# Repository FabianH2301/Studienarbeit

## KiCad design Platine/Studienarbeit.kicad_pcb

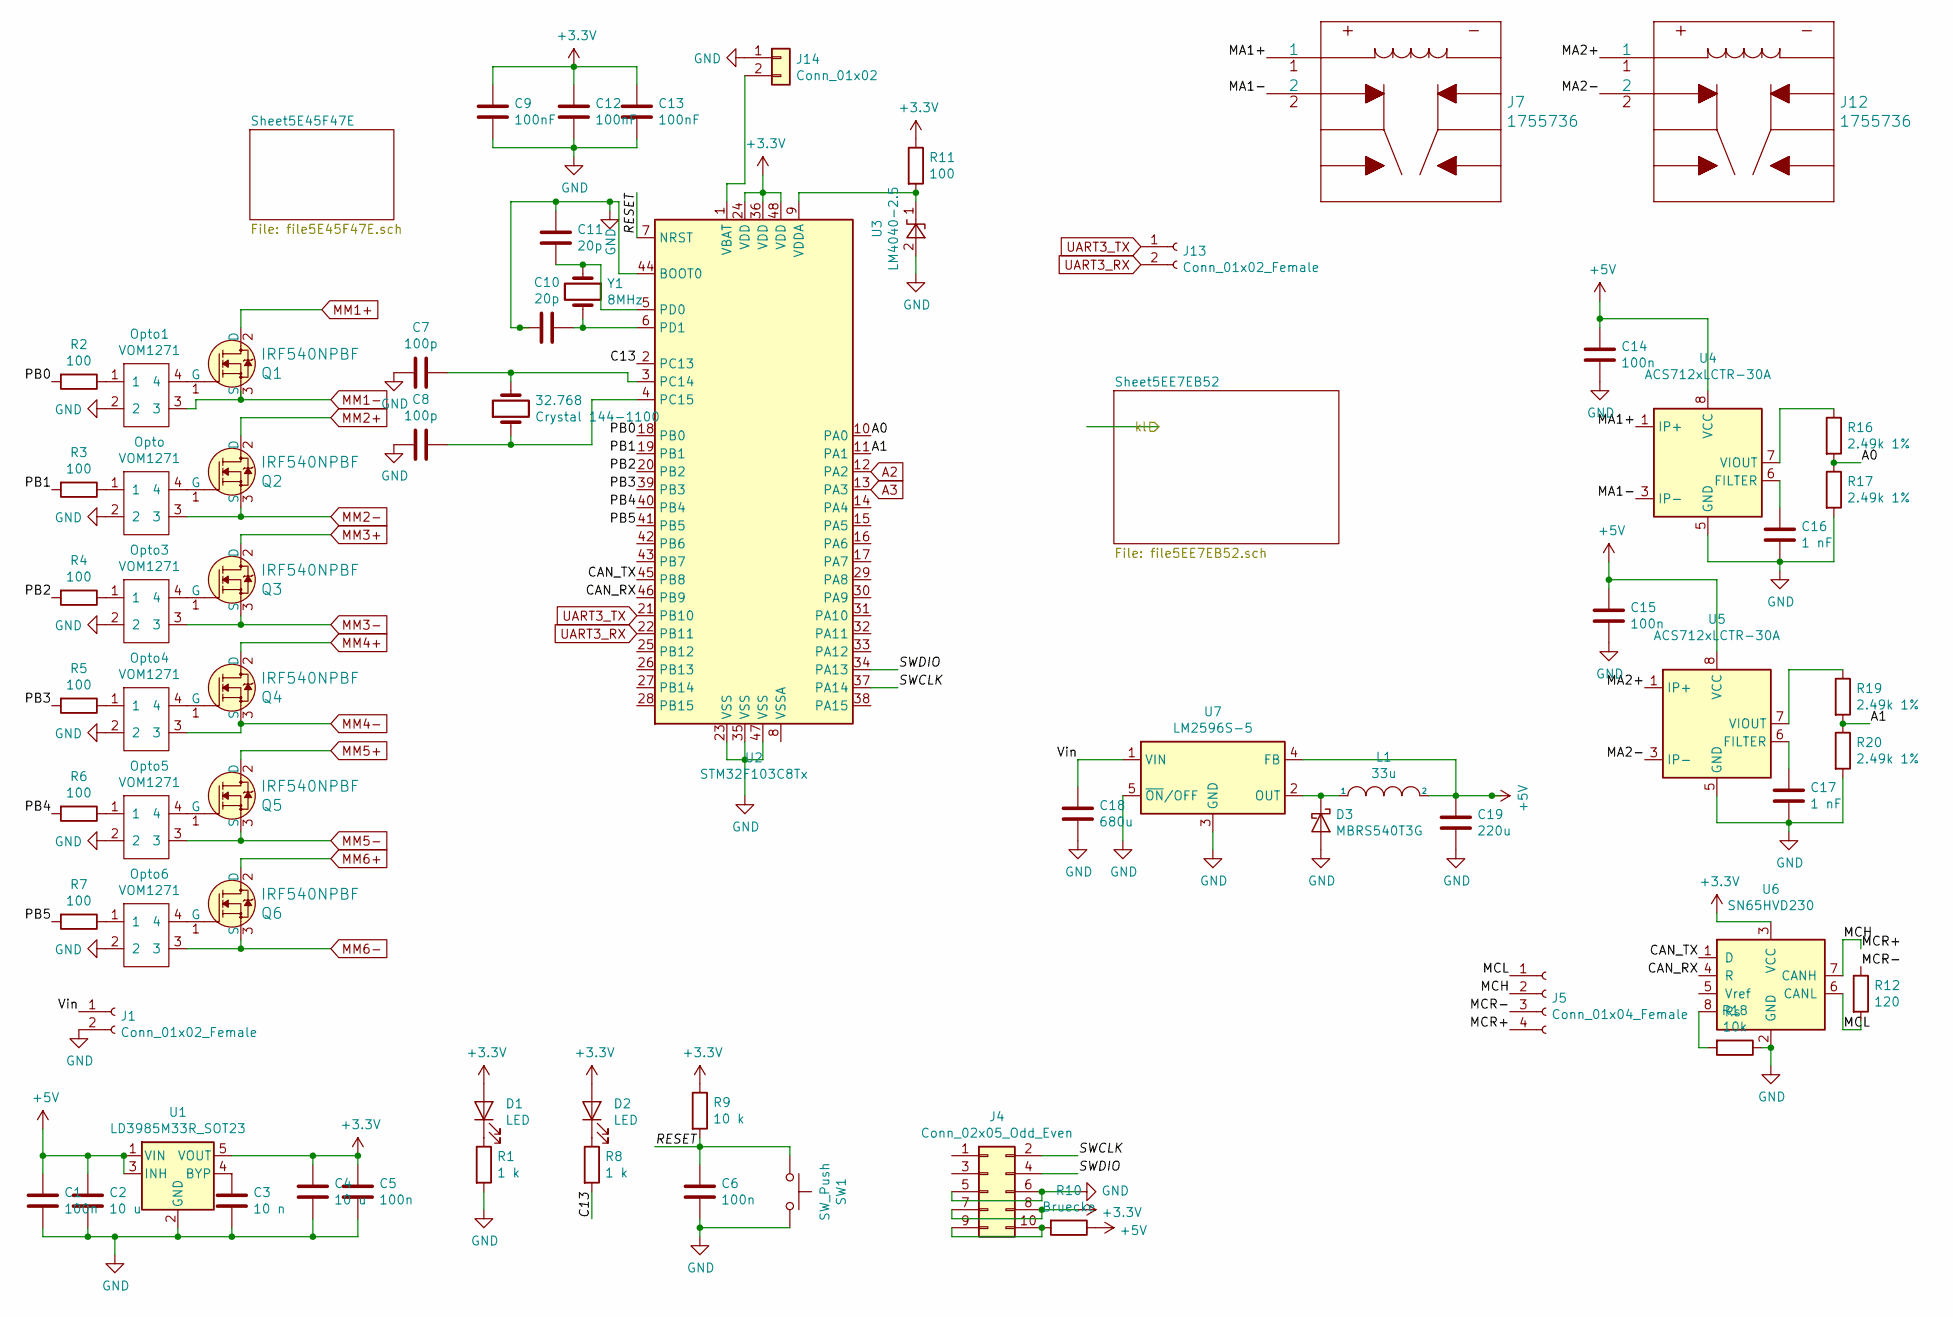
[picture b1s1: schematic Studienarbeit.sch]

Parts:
32.768: Crystal 144-1100; Crystal_SMD_2520-4Pin_2.5x2.0mm
C1, C5, C14, C15: 100n; C_0805_2012Metric; LCSC C136621
C2, C4: 10 u; C_0805_2012Metric; LCSC C15850
C3: 10 n; C_0805_2012Metric
C6: 100n; C_0805_2012Metric
C7, C8: 100p; C_0805_2012Metric
C9, C12, C13: 100nF; C_0805_2012Metric; LCSC C136621
C10, C11: 20p; C_0805_2012Metric
C16, C17: 1 nF; C_0805_2012Metric
C18: 680u; C_Elec_10x10.2
C19: 220u; C_Elec_8x6.2
D1, D2: LED; LED_0603_1608Metric; LCSC C2286
D3: MBRS540T3G; D_SMC; LCSC C31849
J1, J13: Conn_01x02_Female; JST_XH_B2B-XH-A_1x02_P2.50mm_Vertical
J4: Conn_02x05_Odd_Even; PinHeader_2x05_P2.54mm_Vertical
J5: Conn_01x04_Female; JST_XH_B4B-XH-A_1x04_P2.50mm_Vertical
J7, J12: 1755736; PhoenixContact1755736
J14: Conn_01x02; PinHeader_1x02_P2.54mm_Vertical
L1: 33u; L_Wuerth_WE-PD-Typ-LS
Opto, Opto1, Opto3, Opto4, Opto5, Opto6: VOM1271; LCSC C146286
Q1, Q2, Q3, Q4, Q5, Q6: IRF540NPBF; TO-220-3_Vertical; MPN IRF540NPBF; Digi-Key_PN IRF540NPBF-ND
R1, R8: 1 k; R_0805_2012Metric; LCSC C17513
R2: 100; R_0805_2012Metric
R3, R4, R5, R6, R7, R11: 100; R_0805_2012Metric; LCSC C17408
R9: 10 k; R_0805_2012Metric; LCSC C17414
R10: Bruecke; R_0805_2012Metric
R12: 120; R_0805_2012Metric; LCSC C17437
R16, R17, R19, R20: 2.49k 1%; R_0805_2012Metric; LCSC C17408
R18: 10k; R_0805_2012Metric; LCSC C17414
SW1: SW_Push; SW_SPST_B3S-1000
U1: LD3985M33R_SOT23; SOT-23-5; LCSC C46243
U2: STM32F103C8Tx; LQFP-48_7x7mm_P0.5mm; LCSC C8734
U3: LM4040-2.5; SOT-23
U4, U5: ACS712xLCTR-30A; SOIC-8_3.9x4.9mm_P1.27mm; LCSC C9932
U6: SN65HVD230; SOIC-8_3.9x4.9mm_P1.27mm; LCSC C12084
U7: LM2596S-5; TO-263-5_TabPin3; LCSC C10002
Y1: 8MHz; Crystal_HC49-4H_Vertical

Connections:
+3V3: C4.1, C5.1, C9.1, C12.1, C13.1, D1.2 (A), D2.2 (A), J4.7, J4.8, R9.1, R11.1, U1.5 (VOUT), U2.24 (VDD), U2.36 (VDD), U2.48 (VDD), U6.3 (VCC)
+5V: C1.1, C2.1, C14.2, C15.2, C19.1, L1.2, R10.1, U1.1 (VIN), U1.3 (INH), U4.8 (VCC), U5.8 (VCC), U7.4 (FB); also elsewhere on the board
/A0: R16.2, R17.1, U2.10 (PA0)
/A1: R19.2, R20.1, U2.11 (PA1)
/C13: R8.2, U2.2 (PC13)
/CAN_RX: U2.46 (PB9), U6.4 (R)
/CAN_TX: U2.45 (PB8), U6.1 (D)
/MA1+: J7.1, U4.1 (IP+), U4.2 (IP+)
/MA1-: J7.2, U4.3 (IP-), U4.4 (IP-)
/MA2+: J12.1, U5.1 (IP+), U5.2 (IP+)
/MA2-: J12.2, U5.3 (IP-), U5.4 (IP-)
/MCH: J5.2, J5.4, U6.7 (CANH)
/MCL: J5.1, R12.2, U6.6 (CANL)
/MCR-: J5.3, R12.1
/PB0: R2.2, U2.18 (PB0)
/PB1: R3.2, U2.19 (PB1)
/PB2: R4.2, U2.20 (PB2)
/PB3: R5.2, U2.39 (PB3)
/PB4: R6.2, U2.40 (PB4)
/PB5: R7.2, U2.41 (PB5)
/RESET: C6.1, R9.2, SW1.1, U2.7 (NRST)
/SWCLK: J4.2, U2.37 (PA14)
/SWDIO: J4.4, U2.34 (PA13)
/Vin: C18.1, J1.1, U7.1 (VIN)
A2: U2.12 (PA2); also elsewhere on the board
A3: U2.13 (PA3); also elsewhere on the board
GND: C1.2, C2.2, C3.2, C4.2, C5.2, C6.2, C7.2, C8.2, C9.2, C10.1, C11.1, C12.2, C13.2, C14.1, C15.1, C16.1, C17.1, C18.2, C19.2, D3.2 (A), J1.2, J4.5, J4.6, J14.1, Opto.2, Opto1.2, Opto3.2, Opto4.2, Opto5.2, Opto6.2, R1.2, R17.2, R18.1, R20.2, SW1.2, U1.2 (GND), U2.23 (VSS), U2.35 (VSS), U2.44 (BOOT0), U2.47 (VSS), U3.2 (A), U4.5 (GND), U5.5 (GND), U6.2 (GND), U7.3 (GND), U7.5 (~ON~/OFF); also elsewhere on the board
MM1+: Q1.2 (D); also elsewhere on the board
MM1-: Opto1.3, Q1.3 (S); also elsewhere on the board
MM2+: Q2.2 (D); also elsewhere on the board
MM2-: Opto.3, Q2.3 (S); also elsewhere on the board
MM3+: Q3.2 (D); also elsewhere on the board
MM3-: Opto3.3, Q3.3 (S); also elsewhere on the board
MM4+: Q4.2 (D); also elsewhere on the board
MM4-: Opto4.3, Q4.3 (S); also elsewhere on the board
MM5+: Q5.2 (D); also elsewhere on the board
MM5-: Opto5.3, Q5.3 (S); also elsewhere on the board
MM6+: Q6.2 (D); also elsewhere on the board
MM6-: Opto6.3, Q6.3 (S); also elsewhere on the board
unnamed: 32.768.1, C8.1, U2.4 (PC15)
unnamed: 32.768.2, C7.1, U2.3 (PC14)
unnamed: C3.1, U1.4 (BYP)
unnamed: C10.2, U2.6 (PD1), Y1.2
unnamed: C11.2, U2.5 (PD0), Y1.1
unnamed: C16.2, U4.6 (FILTER)
unnamed: C17.2, U5.6 (FILTER)
unnamed: D1.1 (K), R1.1
unnamed: D2.1 (K), R8.1
unnamed: D3.1 (K), L1.1, U7.2 (OUT)
unnamed: J4.9, J4.10, R10.2
unnamed: J14.2, U2.1 (VBAT)
unnamed: Opto1.1, R2.1
unnamed: Opto1.4, Q1.1 (G)
unnamed 72: Opto.1, R3.1; also elsewhere on the board
unnamed 73: Opto.4, Q2.1 (G); also elsewhere on the board
unnamed: Opto3.1, R4.1
unnamed: Opto3.4, Q3.1 (G)
unnamed: Opto4.1, R5.1
unnamed: Opto4.4, Q4.1 (G)
unnamed: Opto5.1, R6.1
unnamed: Opto5.4, Q5.1 (G)
unnamed: Opto6.1, R7.1
unnamed: Opto6.4, Q6.1 (G)
unnamed: R11.2, U2.9 (VDDA), U3.1 (K)
unnamed: R16.1, U4.7 (VIOUT)
unnamed: R18.2, U6.8 (Rs)
unnamed: R19.1, U5.7 (VIOUT)
UART3_RX: J13.2, U2.22 (PB11)
UART3_TX: J13.1, U2.21 (PB10)

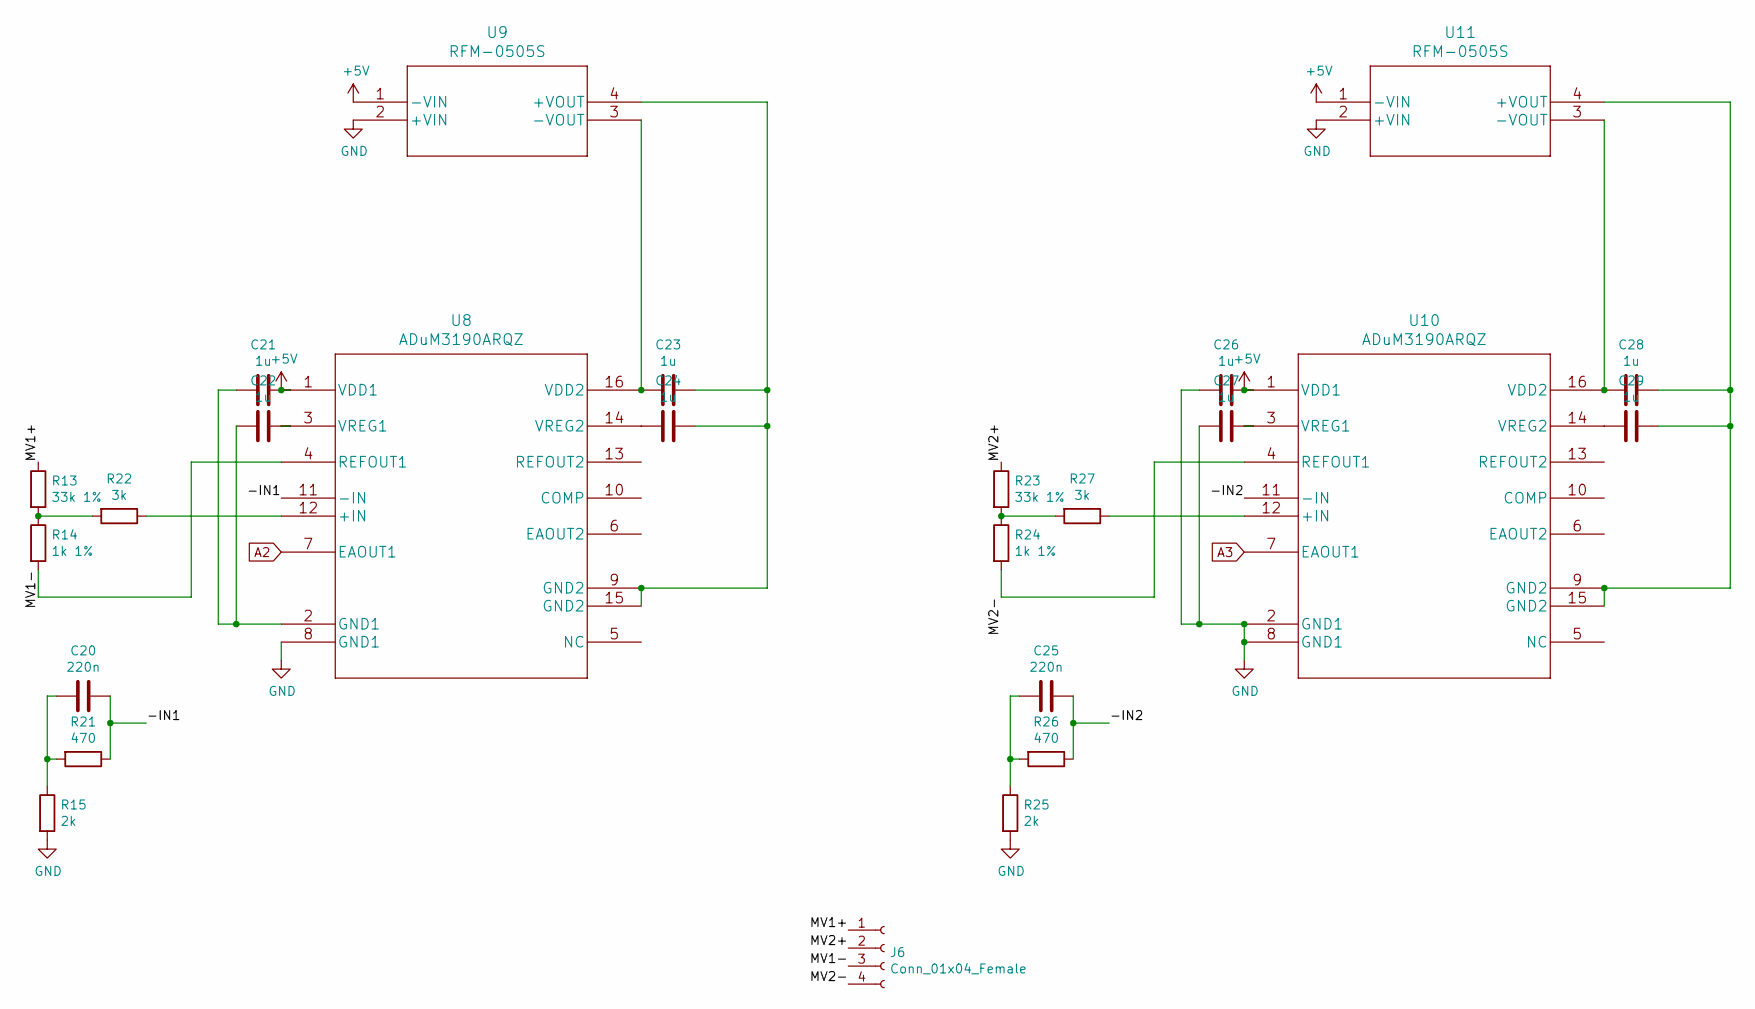
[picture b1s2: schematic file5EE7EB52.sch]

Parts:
C20, C25: 220n; C_0805_2012Metric; LCSC C5378
C21, C22, C23, C24, C26, C27, C28, C29: 1u; C_0805_2012Metric; LCSC C28323
J6: Conn_01x04_Female; JST_XH_B4B-XH-A_1x04_P2.50mm_Vertical
R13, R23: 33k 1%; R_0805_2012Metric; LCSC C17633
R14, R24: 1k 1%; R_0805_2012Metric; LCSC C17513
R15, R25: 2k; R_0805_2012Metric; LCSC C17604
R21, R26: 470; R_0805_2012Metric; LCSC C17710
R22, R27: 3k; R_0805_2012Metric; LCSC C17661
U8, U10: ADuM3190ARQZ
U9, U11: RFM-0505S

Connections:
+5V: C21.2, C26.2, U8.1 (VDD1), U9.1 (-VIN), U10.1 (VDD1), U11.1 (-VIN); also elsewhere on the board
/Sheet5EE7EB52/-IN1: C20.1, R21.1, U8.11 (-IN)
/Sheet5EE7EB52/-IN2: C25.1, R26.1, U10.11 (-IN)
/Sheet5EE7EB52/MV1+: J6.1, R13.1
/Sheet5EE7EB52/MV1-: J6.3, R14.2, U8.4 (REFOUT1)
/Sheet5EE7EB52/MV2+: J6.2, R23.1
/Sheet5EE7EB52/MV2-: J6.4, R24.2, U10.4 (REFOUT1)
A2: U8.7 (EAOUT1); also elsewhere on the board
A3: U10.7 (EAOUT1); also elsewhere on the board
GND: C26.1, C27.1, R15.2, R25.2, U8.8 (GND1), U9.2 (+VIN), U10.2 (GND1), U10.8 (GND1), U11.2 (+VIN); also elsewhere on the board
unnamed: C20.2, R15.1, R21.2
unnamed: C21.1, C22.1, U8.2 (GND1)
unnamed: C22.2, U8.3 (VREG1)
unnamed: C23.1, U8.16 (VDD2), U9.3 (-VOUT)
unnamed: C23.2, C24.2, U8.9 (GND2), U8.15 (GND2), U9.4 (+VOUT)
unnamed: C24.1, U8.14 (VREG2)
unnamed: C25.2, R25.1, R26.2
unnamed: C27.2, U10.3 (VREG1)
unnamed: C28.1, U10.16 (VDD2), U11.3 (-VOUT)
unnamed: C28.2, C29.2, U10.9 (GND2), U10.15 (GND2), U11.4 (+VOUT)
unnamed: C29.1, U10.14 (VREG2)
unnamed: R13.2, R14.1, R22.2
unnamed: R22.1, U8.12 (+IN)
unnamed: R23.2, R24.1, R27.2
unnamed: R27.1, U10.12 (+IN)

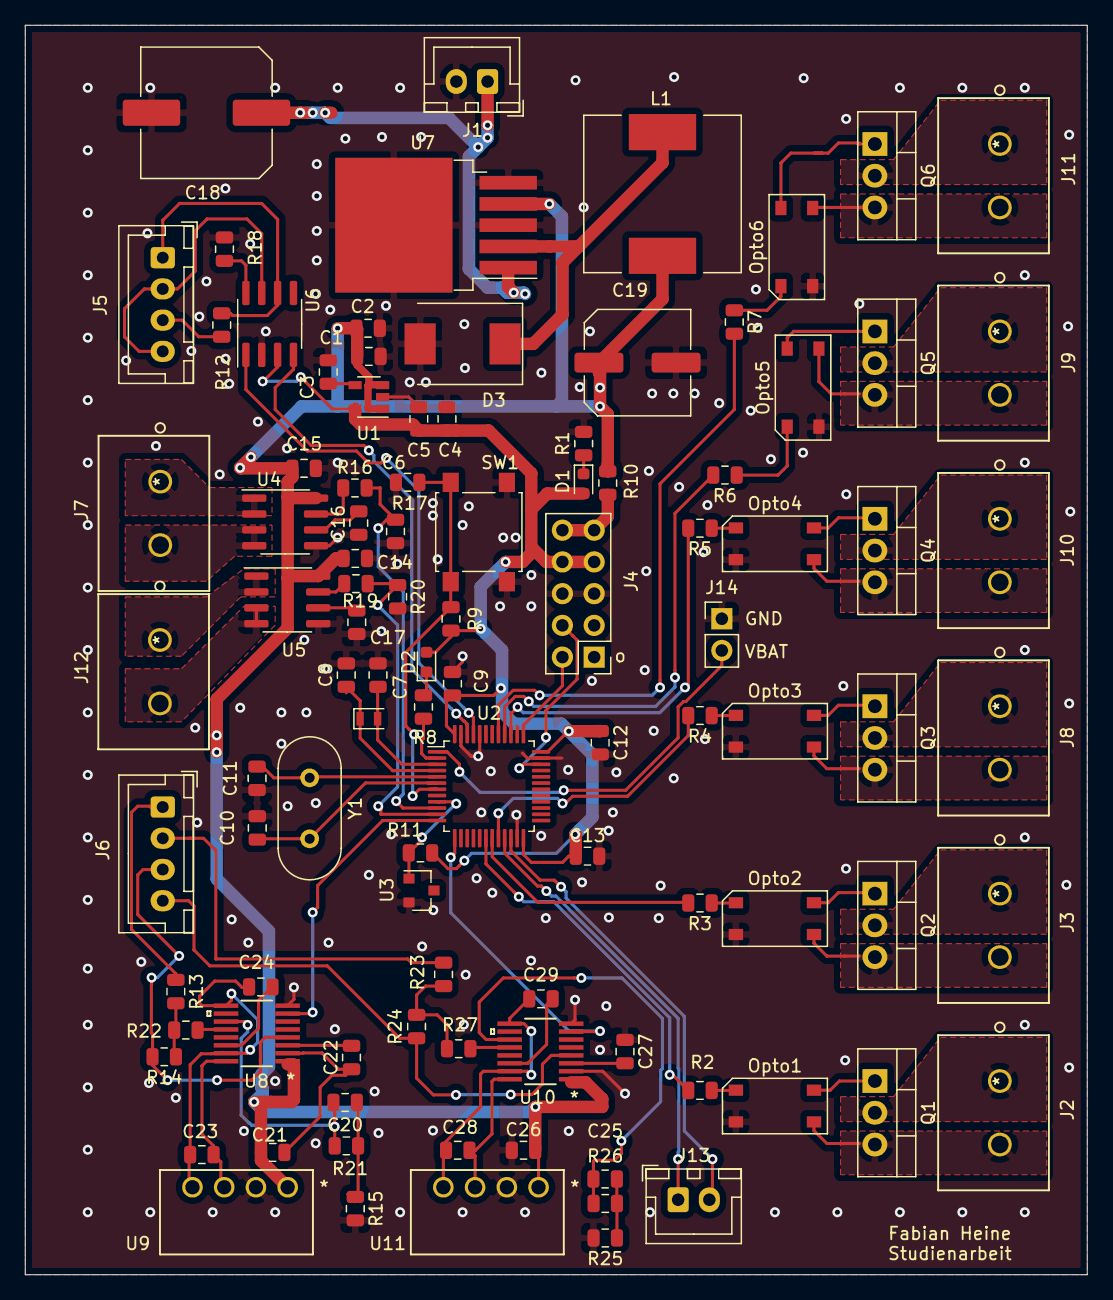
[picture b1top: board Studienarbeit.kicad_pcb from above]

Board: 2 copper layers, 85.0 x 100.0 mm, 100 parts (0 on the bottom side), 90 nets.

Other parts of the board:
J2, J3, J8, J9, J10, J11: 1755736; PhoenixContact1755736
Opto2: VOM1271

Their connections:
GND: Opto2.2; also elsewhere on the board
MM1+: J2.1; also elsewhere on the board
MM1-: J2.2; also elsewhere on the board
MM2+: J3.1; also elsewhere on the board
MM2-: J3.2, Opto2.3; also elsewhere on the board
MM3+: J8.1; also elsewhere on the board
MM3-: J8.2; also elsewhere on the board
MM4+: J10.1; also elsewhere on the board
MM4-: J10.2; also elsewhere on the board
MM5+: J9.1; also elsewhere on the board
MM5-: J9.2; also elsewhere on the board
MM6+: J11.1; also elsewhere on the board
MM6-: J11.2; also elsewhere on the board
unnamed 72: Opto2.1; also elsewhere on the board
unnamed 73: Opto2.4; also elsewhere on the board

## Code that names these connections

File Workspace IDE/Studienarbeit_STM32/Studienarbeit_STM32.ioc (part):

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Mcu.Name=STM32F103C(8-B)Tx
Mcu.Package=LQFP48
Mcu.UserName=STM32F103C8Tx
PA13.Mode=Serial_Wire
PA13.Signal=SYS_JTMS-SWDIO
PA14.Mode=Serial_Wire
PA14.Signal=SYS_JTCK-SWCLK
PB5.Signal=GPIO_Output
PB6.Signal=GPIO_Output
PB7.Signal=GPIO_Output
PB8.Mode=Master
PB8.Signal=CAN_RX
PB9.Mode=Master
PB9.Signal=CAN_TX
PC13-TAMPER-RTC.Signal=GPIO_Output
PC14-OSC32_IN.Signal=RCC_OSC32_IN
PC15-OSC32_OUT.Signal=RCC_OSC32_OUT
PD0-OSC_IN.Mode=HSE-External-Oscillator
PD0-OSC_IN.Signal=RCC_OSC_IN
PD1-OSC_OUT.Mode=HSE-External-Oscillator
PD1-OSC_OUT.Signal=RCC_OSC_OUT
RCC.SYSCLKFreq_VALUE=72000000
RCC.SYSCLKSource=RCC_SYSCLKSOURCE_PLLCLK
board=custom

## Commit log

2020-02-04 Initial SetUp
2020-02-04 KICAD Dateien
2020-02-04 Initial Ordnerstruktur
2020-02-04 To much for description
2020-02-08 Platine
2020-02-10 To much to detect
2020-02-10 Pflichtenheft editiert
2020-02-10 Platine fertig geroutet
    ToDO:
    5mm Leiterbahnbreite anpassen
    GND Verbindungen vollständig herstellen
    Kondensatoren prüfen SMD!!
2020-02-13 platine final ready to order
2020-02-13 Platine fertig

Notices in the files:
parts and their libraries:
Copyright 2016 Accelerated Designs. All rights reserved.
